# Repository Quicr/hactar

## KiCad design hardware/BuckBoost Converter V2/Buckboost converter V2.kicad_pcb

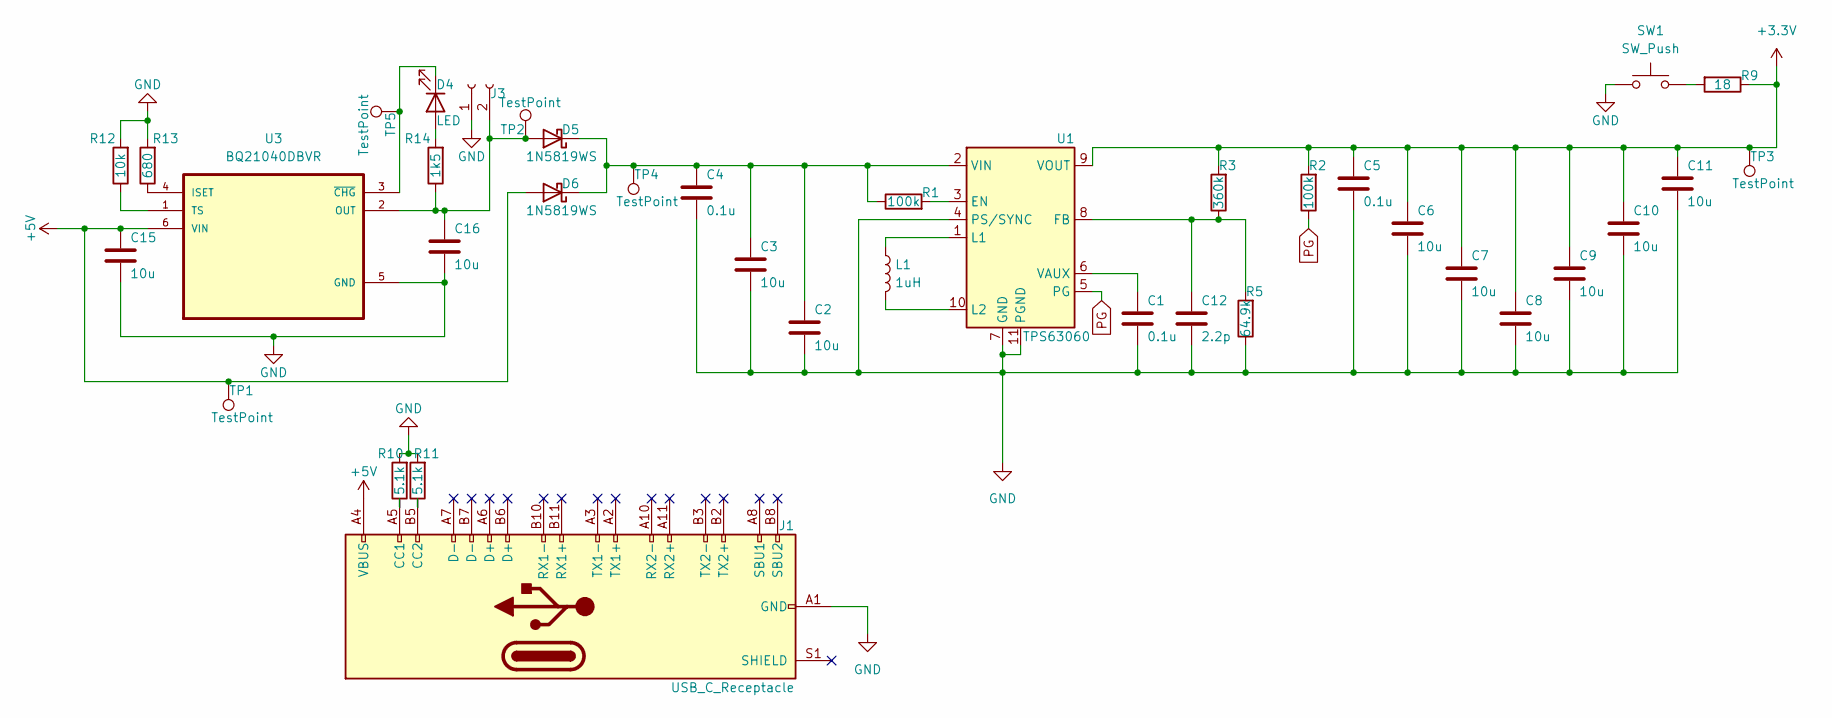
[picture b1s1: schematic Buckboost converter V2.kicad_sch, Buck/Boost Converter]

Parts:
C1, C4, C5: 0.1u; C_0805_2012Metric
C2, C3, C6, C7, C8, C9, C10, C11, C15, C16: 10u; C_0805_2012Metric
C12: 2.2p; C_0805_2012Metric
D4: LED; D_0805_2012Metric
D5, D6: 1N5819WS; D_SOD-323
J1: USB_C_Receptacle; USB_C_Receptacle_HRO_TYPE-C-31-M-12
J3: Conn_01x02_Socket; JST_PH_S2B-PH-SM4-TB_1x02-1MP_P2.00mm_Horizontal
L1: 1uH; L_0805_2012Metric
R1, R2: 100k; R_0402_1005Metric
R3: 360k; R_0402_1005Metric
R5: 64.9k; R_0402_1005Metric
R9: 18; R_1218_3246Metric
R10, R11: 5.1k; R_0402_1005Metric
R12: 10k; R_0805_2012Metric
R13: 680; R_0805_2012Metric
R14: 1k5; R_0805_2012Metric
SW1: SW_Push; SW_DIP_SPSTx01_Slide_6.7x4.1mm_W6.73mm_P2.54mm_LowProfile_J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
TP1, TP2, TP3, TP4, TP5: TestPoint; TestPoint_THTPad_D2.0mm_Drill1.0mm
U1: TPS63060; Texas_S-PWSON-N10_ThermalVias
U3: BQ21040DBVR; SOT95P280X145-6N

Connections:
+3.3V: C5.1, C6.1, C7.1, C8.1, C9.1, C10.1, C11.1, R2.2, R3.2, R9.1, TP3.1, U1.9 (VOUT)
+5V: C15.1, D6.2 (A), J1.A4 (VBUS), J1.A9 (VBUS), J1.B4 (VBUS), J1.B9 (VBUS), TP1.1, U3.6 (VIN)
GND: C1.2, C2.2, C3.2, C4.2, C5.2, C6.2, C7.2, C8.2, C9.2, C10.2, C11.2, C12.2, C15.2, C16.2, J1.A1 (GND), J1.A12 (GND), J1.B1 (GND), J1.B12 (GND), J3.1, R5.1, R10.2, R11.2, R12.2, R13.2, SW1.1, U1.4 (PS/SYNC), U1.7 (GND), U1.11 (PGND), U3.5 (GND)
unnamed: D4.2 (A), R14.2
unnamed: D4.1 (K), TP5.1, U3.3 (~CHG)
unnamed: C16.1, D5.2 (A), J3.2, R14.1, TP2.1, U3.2 (OUT)
unnamed: C2.1, C3.1, C4.1, D5.1 (K), D6.1 (K), R1.1, TP4.1, U1.2 (VIN)
unnamed: J1.A5 (CC1), R10.1
unnamed: J1.B5 (CC2), R11.1
unnamed: R9.2, SW1.2
unnamed: R1.2, U1.3 (EN)
unnamed: C12.1, R3.1, R5.2, U1.8 (FB)
unnamed: L1.1, U1.1 (L1)
unnamed: L1.2, U1.10 (L2)
unnamed: C1.1, U1.6 (VAUX)
unnamed: R13.1, U3.4 (ISET)
unnamed: R12.1, U3.1 (TS)
PG: R2.1, U1.5 (PG)

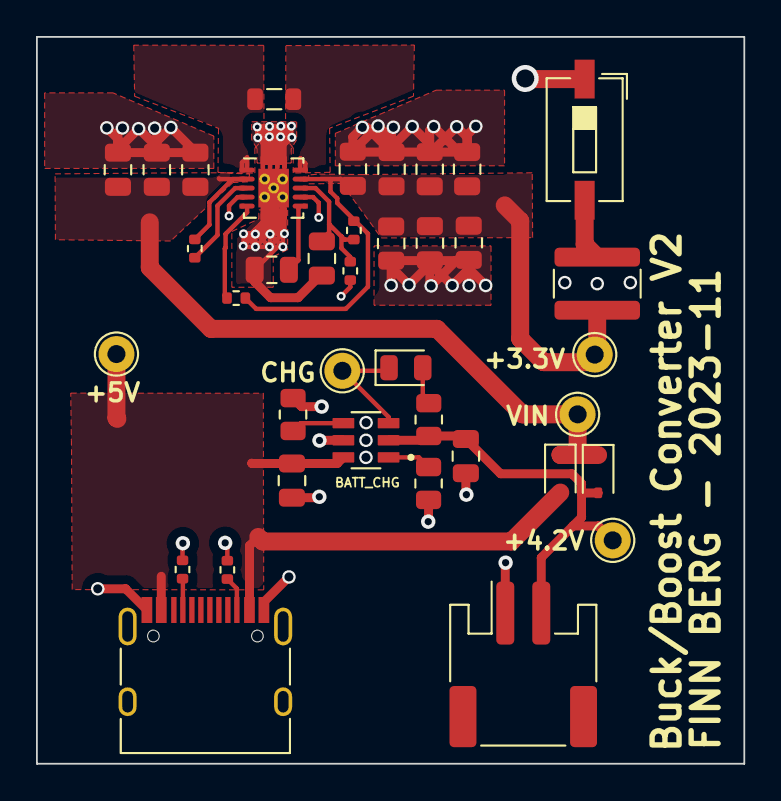
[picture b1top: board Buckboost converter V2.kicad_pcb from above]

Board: 2 copper layers, 39.3 x 40.4 mm, 38 parts (0 on the bottom side), 18 nets.

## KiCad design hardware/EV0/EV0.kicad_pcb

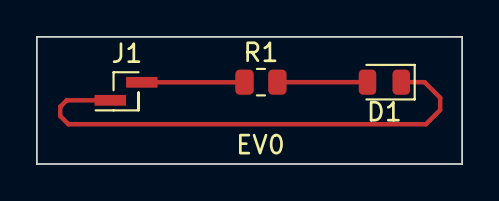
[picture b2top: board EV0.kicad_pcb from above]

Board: 2 copper layers, 23.6 x 7.1 mm, 3 parts (0 on the bottom side), 3 nets.

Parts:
D1: LED; LED_0805_2012Metric
J1: 5V; PinHeader_1x02_P1.00mm_Vertical_SMD_Pin1Right
R1: 470; R_0805_2012Metric

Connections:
unnamed: D1.1 (K), J1.1
unnamed: D1.2 (A), R1.2
unnamed: J1.2, R1.1

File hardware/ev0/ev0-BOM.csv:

"""Designator"";""Package"";""Quantity"";""Designation"";""Supplier and ref"";"
"1;""5V"";""PinHeader_1x02_P2.54mm_Vertical"";1;""5V"";;;"
"2;""D1"";""LED_0805_2012Metric"";1;""LED"";;;"
"3;""R1"";""R_0805_2012Metric"";1;""145"";;;"

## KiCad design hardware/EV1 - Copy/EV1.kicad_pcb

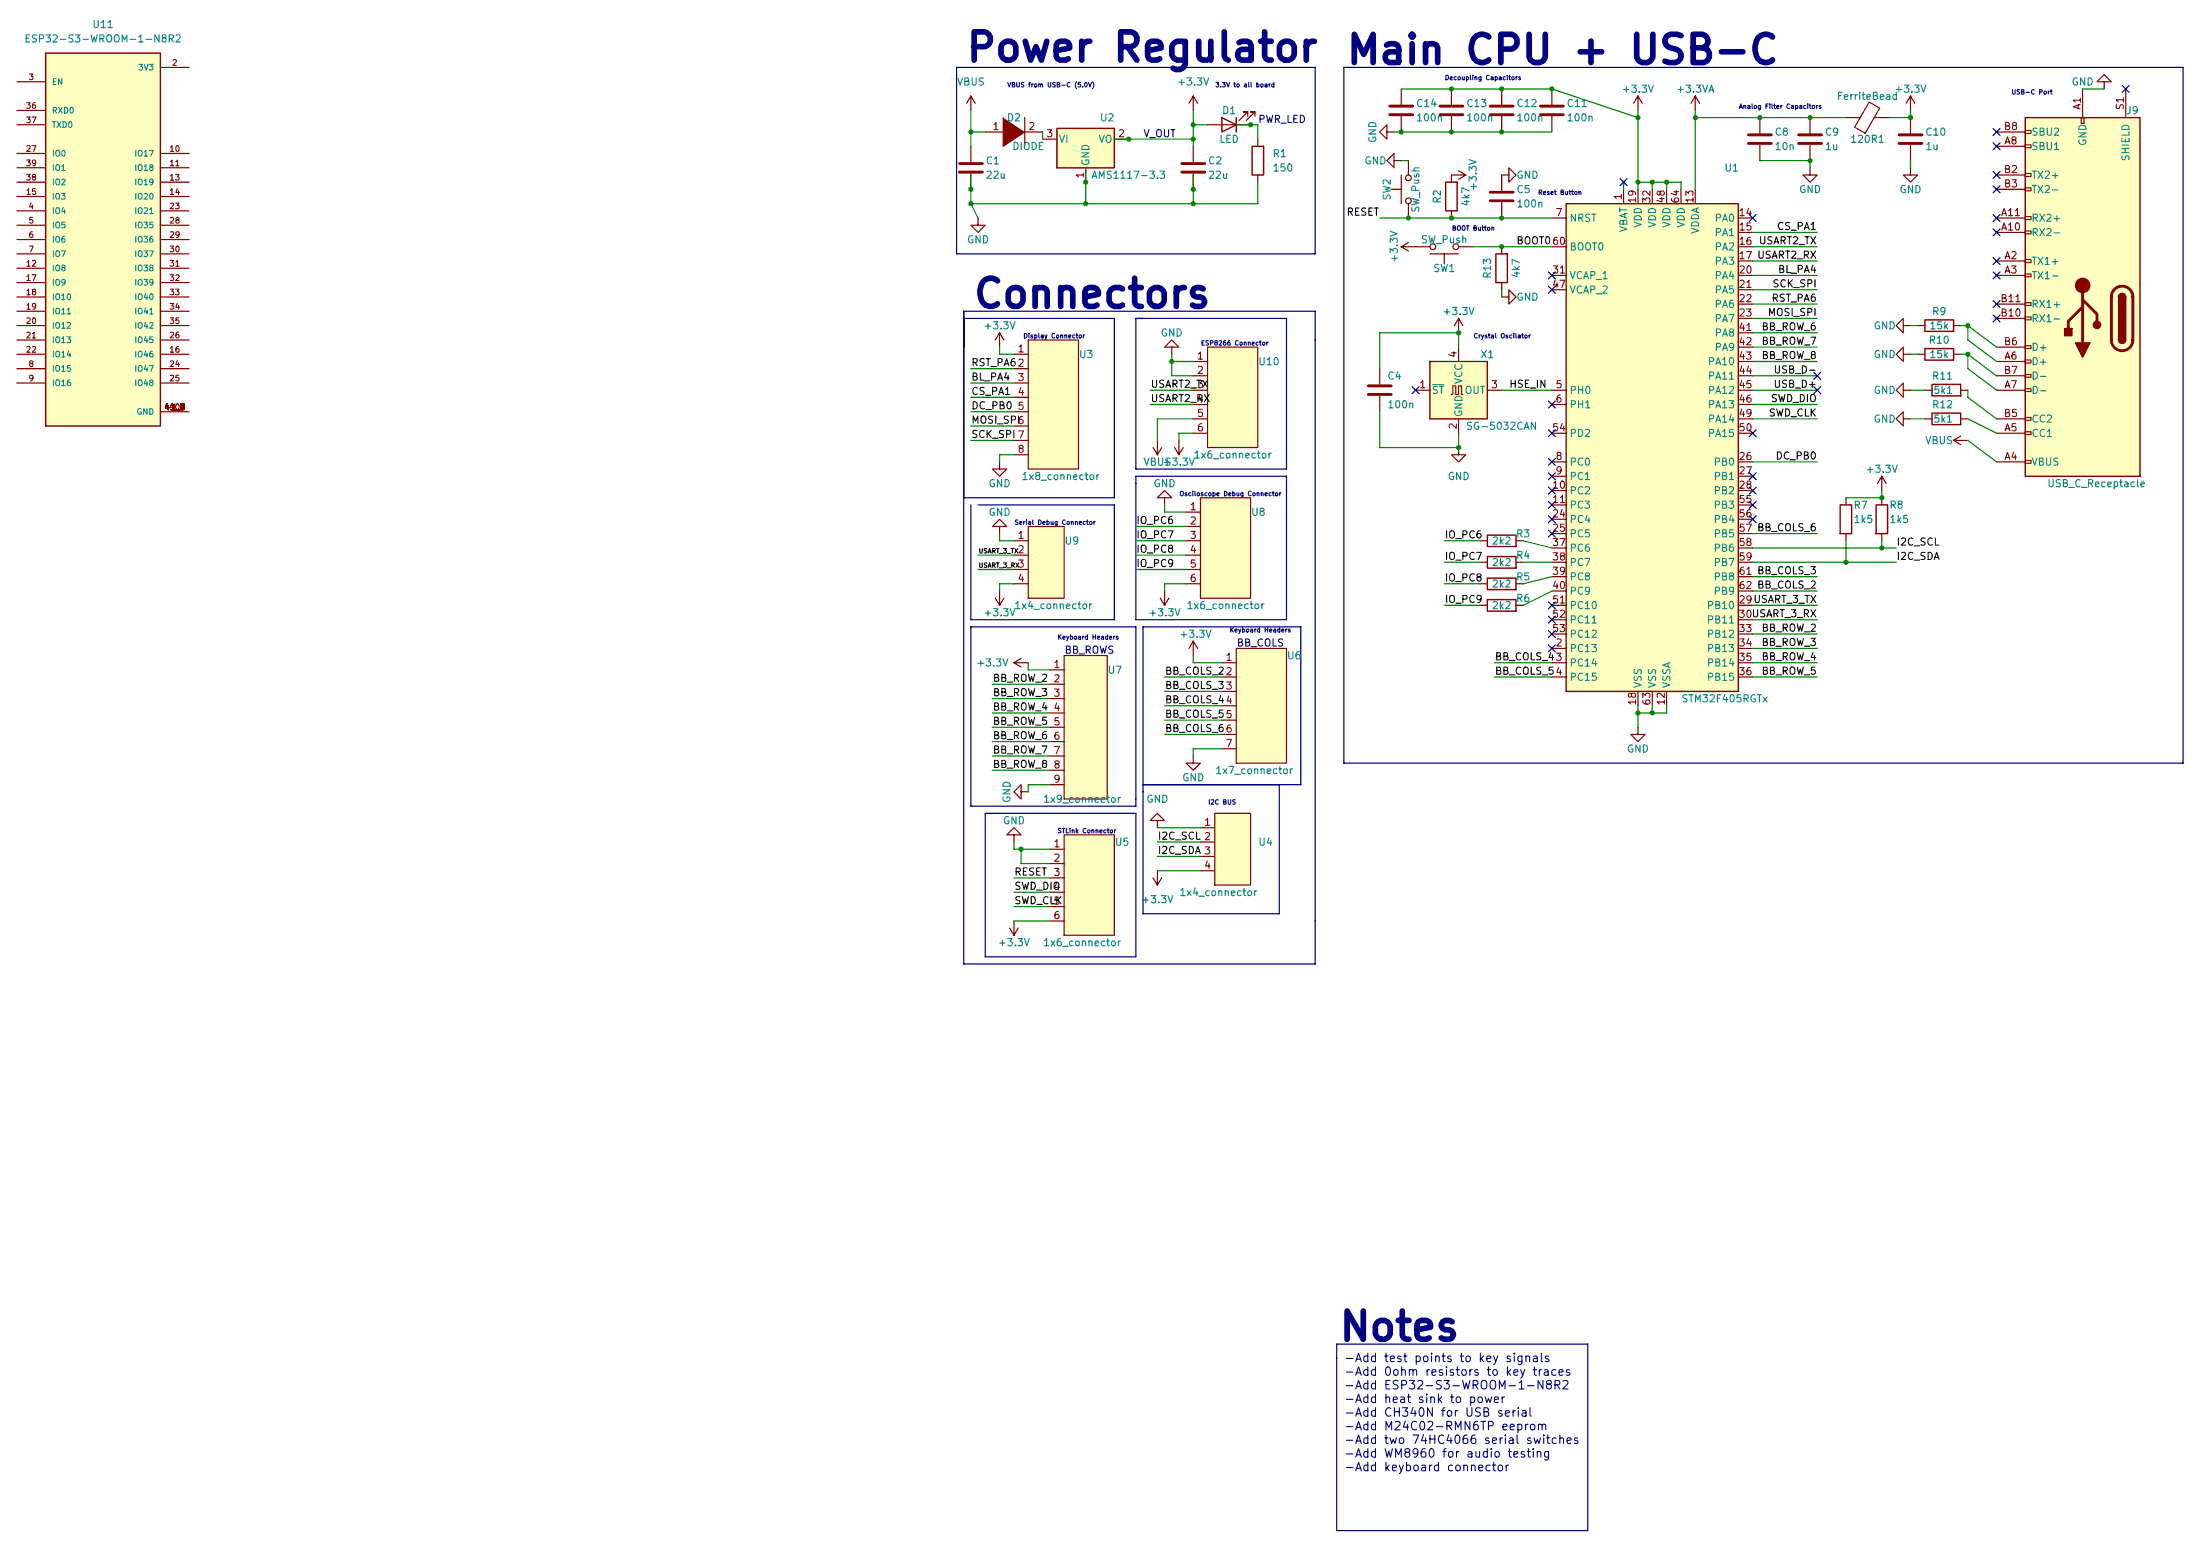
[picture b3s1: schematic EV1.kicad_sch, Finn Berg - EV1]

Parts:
120R1: FerriteBead; L_0805_2012Metric
C1, C2: 22u; C_0805_2012Metric
C4, C5, C11, C12, C13, C14: 100n; C_0805_2012Metric
C8: 10n; C_0805_2012Metric
C9, C10: 1u; C_0805_2012Metric
D1: LED; LED_0805_2012Metric
D2: DIODE; D_0805_2012Metric
J9: USB_C_Receptacle; USB_C_Receptacle_HRO_TYPE-C-31-M-12
R1: 150; R_0805_2012Metric
R2, R13: 4k7; R_0805_2012Metric
R3, R4, R5, R6: 2k2; R_0805_2012Metric
R7, R8: 1k5; R_0805_2012Metric
R9, R10: 15k; R_0805_2012Metric
R11, R12: 5k1; R_0805_2012Metric
SW1, SW2: SW_Push; SW_DIP_SPSTx01_Slide_6.7x4.1mm_W6.73mm_P2.54mm_LowProfile_J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
U1: STM32F405RGTx; LQFP-64_10x10mm_P0.5mm
U2: AMS1117-3.3; SOT-223-3_TabPin2
U3: 1x8_connector; 1X8_CONNECTOR
U4, U9: 1x4_connector
U5, U8, U10: 1x6_connector
U6: 1x7_connector
U7: 1x9_connector
U11: ESP32-S3-WROOM-1-N8R2
X1: SG-5032CAN; Oscillator_SMD_SeikoEpson_SG8002LB-4Pin_5.0x3.2mm

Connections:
+3.3V: 120R1.2, C2.1, C4.1, C10.1, C11.1, C12.1, C13.1, C14.1, D1.2 (A), R2.2, R7.1, R8.1, SW1.1, U1.19 (VDD), U1.32 (VDD), U1.48 (VDD), U1.64 (VDD), U2.2 (VO), U3.1, U4.4, U5.6, U6.1, U7.1, U8.6, U9.4, U10.6, X1.4 (VCC)
+3.3VA: 120R1.1, C8.1, C9.1, U1.13 (VDDA)
/BB_COLS_2: U1.62 (PB9), U6.2
/BB_COLS_3: U1.61 (PB8), U6.3
/BB_COLS_4: U1.3 (PC14), U6.4
/BB_COLS_5: U1.4 (PC15), U6.5
/BB_COLS_6: U1.57 (PB5), U6.6
/BB_ROW_2: U1.33 (PB12), U7.2
/BB_ROW_3: U1.34 (PB13), U7.3
/BB_ROW_4: U1.35 (PB14), U7.4
/BB_ROW_5: U1.36 (PB15), U7.5
/BB_ROW_6: U1.41 (PA8), U7.6
/BB_ROW_7: U1.42 (PA9), U7.7
/BB_ROW_8: U1.43 (PA10), U7.8
/BL_PA4: U1.20 (PA4), U3.3
/BOOT0: R13.2, SW1.2, U1.60 (BOOT0)
/CS_PA1: U1.15 (PA1), U3.4
/DC_PB0: U1.26 (PB0), U3.5
/HSE_IN: U1.5 (PH0), X1.3 (OUT)
/I2C_SCL: R8.2, U1.58 (PB6), U4.2
/I2C_SDA: R7.2, U1.59 (PB7), U4.3
/IO_PC6: R3.1, U8.2
/IO_PC7: R4.1, U8.3
/IO_PC8: R5.1, U8.4
/IO_PC9: R6.1, U8.5
/MOSI_SPI: U1.23 (PA7), U3.6
/RESET: C5.2, R2.1, SW2.2, U1.7 (NRST), U5.3
/RST_PA6: U1.22 (PA6), U3.2
/SCK_SPI: U1.21 (PA5), U3.7
/SWD_CLK: U1.49 (PA14), U5.5
/SWD_DIO: U1.46 (PA13), U5.4
/USART2_RX: U1.17 (PA3), U10.4
/USART2_TX: U1.16 (PA2), U10.3
/USART_3_RX: U1.30 (PB11), U9.3
/USART_3_TX: U1.29 (PB10), U9.2
/USB_D+: U1.45 (PA12)
/USB_D-: U1.44 (PA11)
GND: C1.2, C2.2, C4.2, C5.1, C8.2, C9.2, C10.2, C11.2, C12.2, C13.2, C14.2, J9.A1 (GND), J9.A12 (GND), J9.B1 (GND), J9.B12 (GND), R1.1, R9.1, R10.1, R11.1, R12.1, R13.1, SW2.1, U1.12 (VSSA), U1.18 (VSS), U1.63 (VSS), U2.1 (GND), U3.8, U4.1, U5.1, U5.2, U6.7, U7.9, U8.1, U9.1, U10.1, U10.2, X1.2 (GND)
unnamed: D1.1 (K), R1.2
unnamed: D2.2 (A), U2.3 (VI)
unnamed: J9.A5 (CC1), R12.2
unnamed: J9.A6 (D+), J9.B6 (D+), R9.2
unnamed: J9.A7 (D-), J9.B7 (D-), R10.2
unnamed: J9.B5 (CC2), R11.2
unnamed: R3.2, U1.37 (PC6)
unnamed: R4.2, U1.38 (PC7)
unnamed: R5.2, U1.39 (PC8)
unnamed: R6.2, U1.40 (PC9)
unnamed: U11.1 (GND), U11.40 (GND), U11.41_1 (GND), U11.41_2 (GND), U11.41_3 (GND), U11.41_4 (GND), U11.41_5 (GND), U11.41_6 (GND), U11.41_7 (GND), U11.41_8 (GND), U11.41_9 (GND)
VBUS: C1.1, D2.1 (K), J9.A4 (VBUS), J9.A9 (VBUS), J9.B4 (VBUS), J9.B9 (VBUS), U10.5

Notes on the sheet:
Notes
Osciloscope Debug Connector
BOOT Button
STLink Connector
-Add test points to key signals -Add 0ohm resistors to key traces -Add ESP32-S3-WROOM-1-N8R2 -Add heat sink to power -Add CH340N for USB serial -Add M24C02-RMN6TP eeprom -Add two 74HC4066 serial switches -Add WM8960 for audio testing -Add keyboard connector
Power Regulator
V_OUT
BB_ROWS
Display Connector
Main CPU + USB-C
BB_COLS
PWR_LED
Keyboard Headers
Decoupling Capacitors
Reset Button
Serial Debug Connector
VBUS from USB-C (5.0V)
Connectors
3.3V to all board
Analog Filter Capacitors
I2C BUS
Crystal Oscilator
ESP8266 Connector
USB-C Port

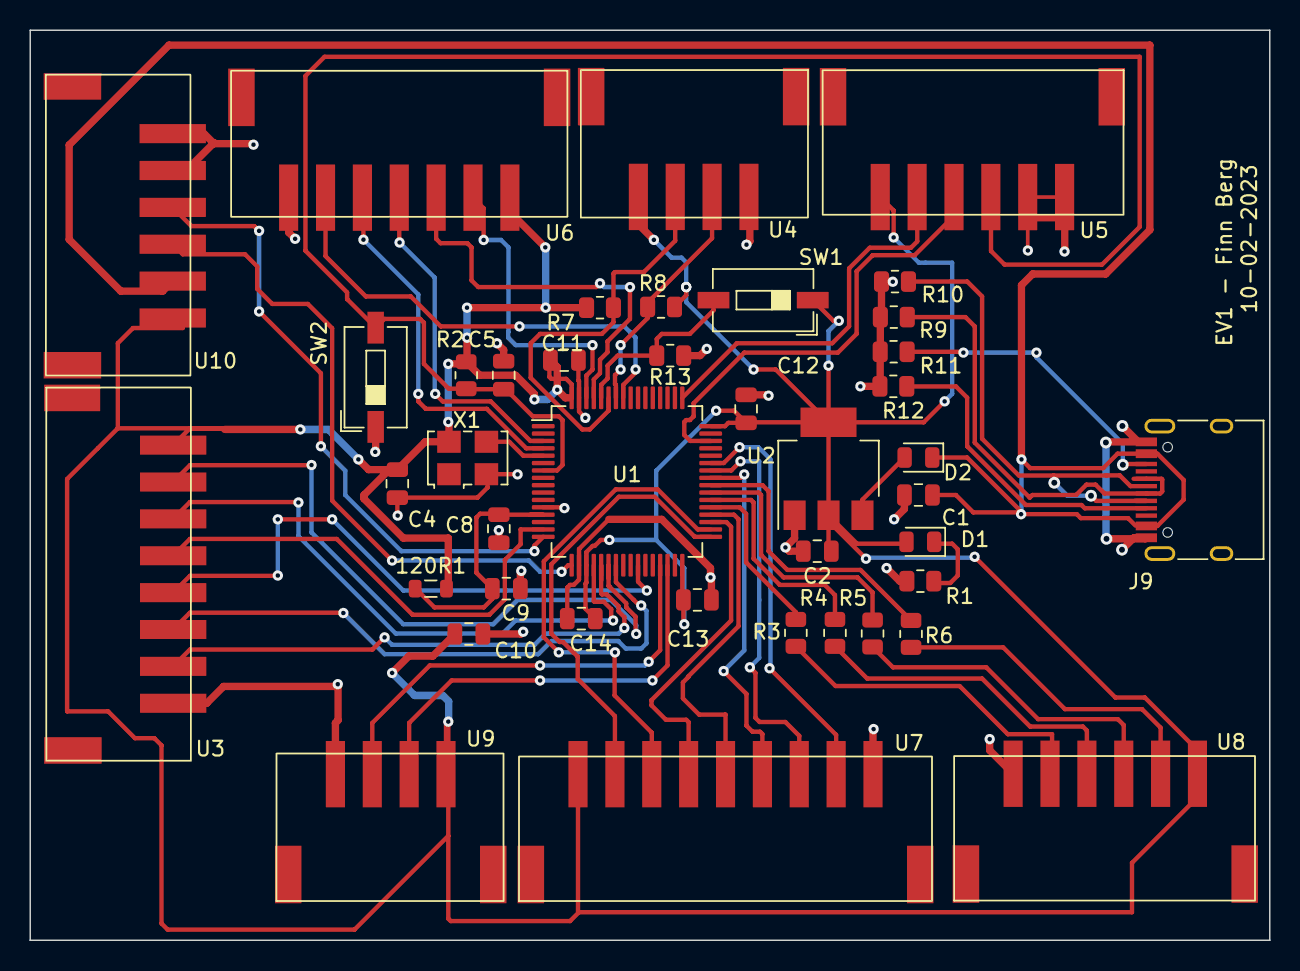
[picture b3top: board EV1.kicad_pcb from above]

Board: 2 copper layers, 84.0 x 61.7 mm, 41 parts (0 on the bottom side), 47 nets.

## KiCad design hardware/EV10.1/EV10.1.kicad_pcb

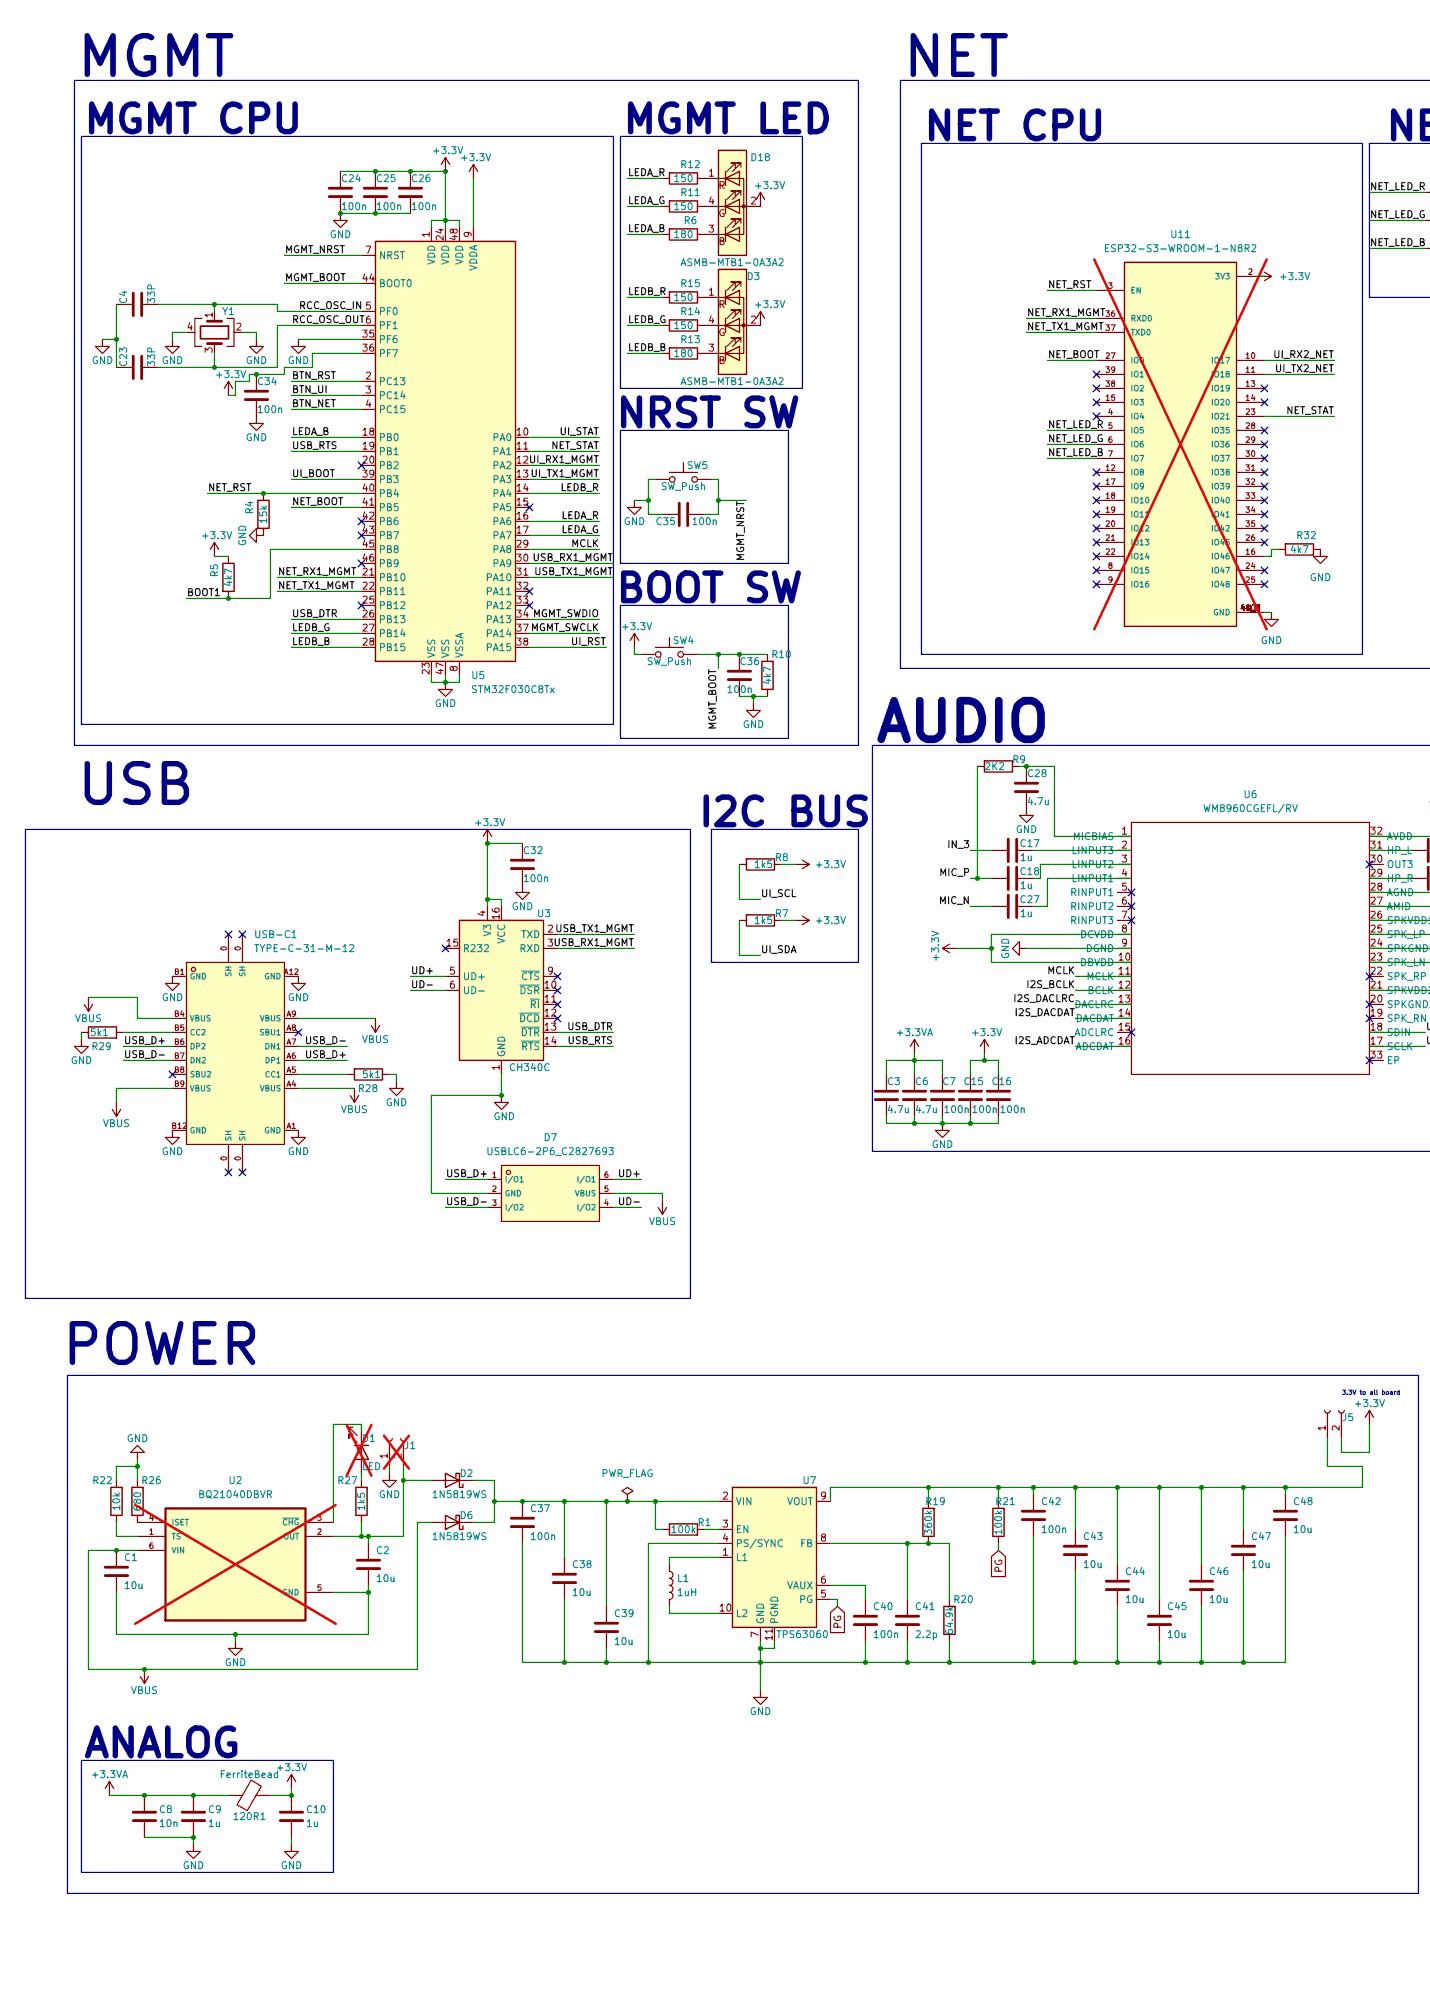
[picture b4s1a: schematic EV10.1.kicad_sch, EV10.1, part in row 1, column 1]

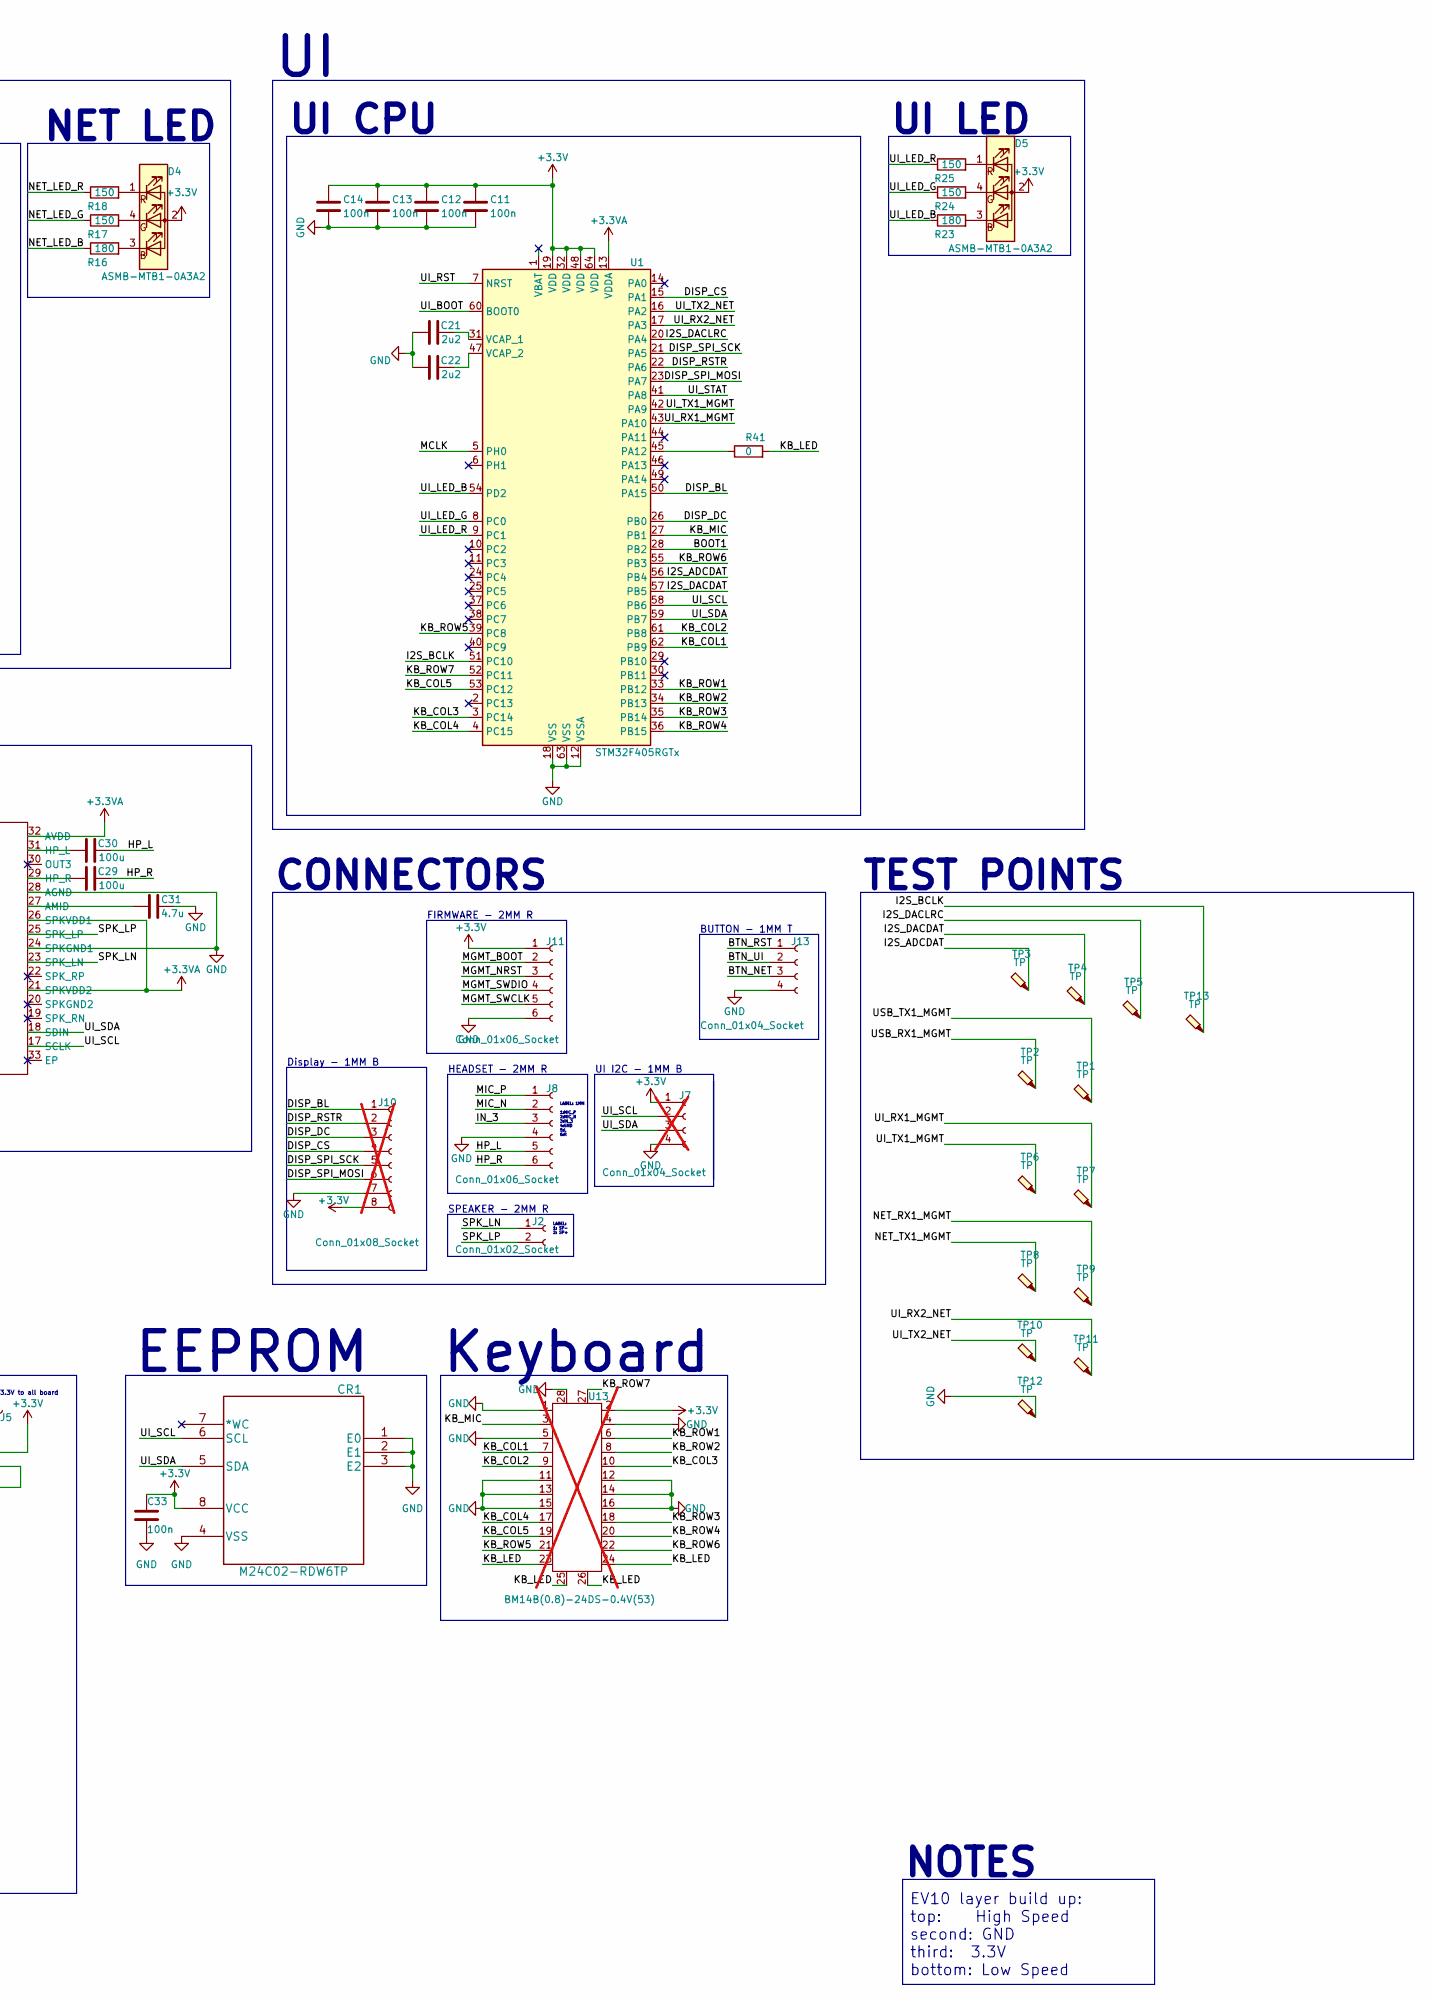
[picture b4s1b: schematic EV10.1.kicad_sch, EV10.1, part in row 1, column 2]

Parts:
120R1: FerriteBead; L_0603_1608Metric; JLCPCB# C127301
C1, C2: 10u; C_0402_1005Metric; JLCPCB# C15525
C3, C6, C28, C31: 4.7u; C_0402_1005Metric; JLCPCB# C23733
C4, C23: 33P; C_0805_2012Metric; JLCPCB# C107115
C7, C11, C12, C13, C14, C15, C16, C24, C25, C26, C32, C33, C34, C35, C36: 100n; C_0402_1005Metric; JLCPCB# C1525
C8: 10n; C_0402_1005Metric; JLCPCB# C15195
C9, C10, C17, C18, C27: 1u; C_0402_1005Metric; JLCPCB# C52923
C21, C22: 2u2; C_0402_1005Metric; JLCPCB# C12530
C29, C30: 100u; C_1206_3216Metric; JLCPCB# C15008
C37, C40, C42: 100n; C_0805_2012Metric; JLCPCB# C49678
C38, C39, C43, C44, C45, C46, C47, C48: 10u; C_0805_2012Metric; JLCPCB# C15850
C41: 2.2p; C_0805_2012Metric; JLCPCB# C519933
CR1: M24C02-RDW6TP; New_ESP32_M24C02-RMN6TP; JLCPCB Rotation Offset -90
D1: LED; D_0805_2012Metric; JLCPCB# C185403; not fitted
D2, D6: 1N5819WS; D_SOD-323; JLCPCB# C191023
D3, D4, D5, D18: ASMB-MTB1-0A3A2; LED RGB; JLCPCB Position Offset 0.70,0.35
D7: USBLC6-2P6_C2827693; SOT-666-6_L1.6-W1.2-P0.50-LS1.6-BL; JLCPCB# C2827693
J1: Conn_01x02_Socket; JST_PH_S2B-PH-SM4-TB_1x02-1MP_P2.00mm_Horizontal; JLCPCB Rotation Offset 180; not fitted
J2, J5: Conn_01x02_Socket; JST_PH_S2B-PH-SM4-TB_1x02-1MP_P2.00mm_Horizontal; JLCPCB Rotation Offset 180
J7: Conn_01x04_Socket; 1x4pin 1mm connector; JLCPCB Position Offset 2.59,1.73; not fitted
J8, J11: Conn_01x06_Socket; JST_PH_S6B-PH-SM4-TB_1x06-1MP_P2.00mm_Horizontal; JLCPCB# C265405
J10: Conn_01x08_Socket; JST_SHL_SM08B-SHLS-TF_1x08-1MP_P1.00mm_Horizontal; JLCPCB# C3029349; not fitted
J13: Conn_01x04_Socket; 1x4pin 1mm connector; JLCPCB Position Offset 2.59,1.73
L1: 1uH; L_0805_2012Metric; JLCPCB# C370013
R1, R21: 100k; R_0402_1005Metric; JLCPCB# C25741
R4: 15k; R_0402_1005Metric; JLCPCB# C25756
R5, R10, R32: 4k7; R_0402_1005Metric; JLCPCB# C25900
R6, R13, R16, R23: 180; R_0402_1005Metric; JLCPCB# C25087
R7, R8, R27: 1k5; R_0402_1005Metric; JLCPCB# C25867
R9: 2K2; R_0402_1005Metric; JLCPCB# C25879
R11, R12, R14, R15, R17, R18, R24, R25: 150; R_0402_1005Metric; JLCPCB# C25082
R19: 360k; R_0402_1005Metric; JLCPCB# C170299
R20: 64.9k; R_0402_1005Metric; JLCPCB# C185403
R22: 10k; R_0402_1005Metric; JLCPCB# C25744
R26: 680; R_0402_1005Metric; JLCPCB# C25130
R28, R29: 5k1; R_0402_1005Metric; JLCPCB# C25905
R41: 0; R_0402_1005Metric; JLCPCB# C17168
SW4, SW5: SW_Push; SW_DIP_SPSTx01_Slide_6.7x4.1mm_W6.73mm_P2.54mm_LowProfile_J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; JLCPCB# C266189
TP1, TP2, TP3, TP4, TP5, TP6, TP7, TP8, TP9, TP10, TP11, TP12, TP13: TP; TestPoint_Keystone_5000-5004_Miniature; JLCPCB# C5199900
U1: STM32F405RGTx; LQFP-64_10x10mm_P0.5mm; JLCPCB# C15742
U2: BQ21040DBVR; SOT-23-6; JLCPCB Rotation Offset 180; not fitted
U3: CH340C; SOIC-16_3.9x9.9mm_P1.27mm; JLCPCB# C84681
U5: STM32F030C8Tx; LQFP-48_7x7mm_P0.5mm; JLCPCB# C80488
U6: WM8960CGEFL/RV; QFN50P500X500X90-33N; JLCPCB# C18752
U7: TPS63060; Texas_S-PWSON-N10_ThermalVias; JLCPCB Rotation Offset -90
U11: ESP32-S3-WROOM-1-N8R2; ESP32-S3-WROOM-1U; JLCPCB# C3013944; not fitted
U13: BM14B(0.8)-24DS-0.4V(53); BM14B(0.B)-24DS-0.4V(53); JLCPCB# C3640874; not fitted
USB-C1: TYPE-C-31-M-12; USB-C_SMD-TYPE-C-31-M-12; JLCPCB Position Offset 0, 1.0
Y1: Crystal_GND24; Crystal_SMD_3225-4Pin_3.2x2.5mm; JLCPCB# C13738

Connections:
+3.3V: 120R1.2, C10.1, C11.1, C12.1, C13.1, C14.1, C15.2, C16.2, C24.1, C25.1, C26.1, C32.1, C33.1, C34.1, CR1.8 (VCC), D3.2 (A), D4.2 (A), D5.2 (A), D18.2 (A), J5.2, J7.1, J10.8, J11.1, R5.1, R7.1, R8.1, SW4.2, U1.19 (VDD), U1.32 (VDD), U1.48 (VDD), U1.64 (VDD), U3.4 (V3), U3.16 (VCC), U5.1 (VDD), U5.9 (VDDA), U5.24 (VDD), U5.36 (PF7), U5.48 (VDD), U6.8 (DCVDD), U6.10 (DBVDD), U11.2 (3V3), U13.2
+3.3VA: 120R1.1, C3.1, C6.1, C7.2, C8.1, C9.1, U1.13 (VDDA), U6.21 (SPKVDD2), U6.26 (SPKVDD1), U6.32 (AVDD)
/BOOT1: R5.2, U1.28 (PB2), U5.45 (PB8)
/BTN_NET: J13.3, U5.4 (PC15)
/BTN_RST: J13.1, U5.2 (PC13)
/BTN_UI: J13.2, U5.3 (PC14)
/DISP_BL: J10.1, U1.50 (PA15)
/DISP_CS: J10.4, U1.15 (PA1)
/DISP_DC: J10.3, U1.26 (PB0)
/DISP_RSTR: J10.2, U1.22 (PA6)
/DISP_SPI_MOSI: J10.6, U1.23 (PA7)
/DISP_SPI_SCK: J10.5, U1.21 (PA5)
/HP_L: C30.2, J8.5
/HP_R: C29.2, J8.6
/I2S_ADCDAT: TP3.1, U1.56 (PB4), U6.16 (ADCDAT)
/I2S_BCLK: TP13.1, U1.51 (PC10), U6.12 (BCLK)
/I2S_DACDAT: TP4.1, U1.57 (PB5), U6.14 (DACDAT)
/I2S_DACLRC: TP5.1, U1.20 (PA4), U6.13 (DACLRC)
/IN_3: C17.1, J8.3
/KB_COL1: U1.62 (PB9), U13.7
/KB_COL2: U1.61 (PB8), U13.9
/KB_COL3: U1.3 (PC14), U13.10
/KB_COL4: U1.4 (PC15), U13.17
/KB_COL5: U1.53 (PC12), U13.19
/KB_LED: R41.2, U13.23, U13.24, U13.25, U13.26
/KB_MIC: U1.27 (PB1), U13.3
/KB_ROW1: U1.33 (PB12), U13.6
/KB_ROW2: U1.34 (PB13), U13.8
/KB_ROW3: U1.35 (PB14), U13.18
/KB_ROW4: U1.36 (PB15), U13.20
/KB_ROW5: U1.39 (PC8), U13.21
/KB_ROW6: U1.55 (PB3), U13.22
/KB_ROW7: U1.52 (PC11), U13.27
/LEDA_B: R6.2, U5.18 (PB0)
/LEDA_G: R11.2, U5.17 (PA7)
/LEDA_R: R12.2, U5.16 (PA6)
/LEDB_B: R13.2, U5.28 (PB15)
/LEDB_G: R14.2, U5.27 (PB14)
/LEDB_R: R15.2, U5.14 (PA4)
/MCLK: U1.5 (PH0), U5.29 (PA8), U6.11 (MCLK)
/MGMT_BOOT: C36.2, J11.2, R10.2, SW4.1, U5.44 (BOOT0)
/MGMT_NRST: C35.2, J11.3, SW5.1, U5.7 (NRST)
/MGMT_SWCLK: J11.5, U5.37 (PA14)
/MGMT_SWDIO: J11.4, U5.34 (PA13)
/MIC_N: C27.1, J8.2
/MIC_P: C18.1, J8.1, R9.2
/NET_BOOT: U5.41 (PB5), U11.27 (IO0)
/NET_LED_B: R16.1, U11.7 (IO7)
/NET_LED_G: R17.1, U11.6 (IO6)
/NET_LED_R: R18.1, U11.5 (IO5)
/NET_RST: R4.1, U5.40 (PB4), U11.3 (EN)
/NET_RX1_MGMT: TP9.1, U5.21 (PB10), U11.36 (RXD0)
/NET_STAT: U5.11 (PA1), U11.23 (IO21)
/NET_TX1_MGMT: TP8.1, U5.22 (PB11), U11.37 (TXD0)
/RCC_OSC_IN: C4.2, U5.5 (PF0), Y1.1
/RCC_OSC_OUT: C23.2, U5.6 (PF1), Y1.3
/SPK_LN: J2.1, U6.23 (SPK_LN)
/SPK_LP: J2.2, U6.25 (SPK_LP)
/UD+: D7.6 (I/O1), U3.5 (UD+)
/UD-: D7.4 (I/O2), U3.6 (UD-)
/UI_BOOT: U1.60 (BOOT0), U5.39 (PB3)
/UI_LED_B: R23.1, U1.54 (PD2)
/UI_LED_G: R24.1, U1.8 (PC0)
/UI_LED_R: R25.1, U1.9 (PC1)
/UI_RST: U1.7 (NRST), U5.38 (PA15)
/UI_RX1_MGMT: TP7.1, U1.43 (PA10), U5.12 (PA2)
/UI_RX2_NET: TP11.1, U1.17 (PA3), U11.10 (IO17)
/UI_SCL: CR1.6 (SCL), J7.2, R8.2, U1.58 (PB6), U6.17 (SCLK)
/UI_SDA: CR1.5 (SDA), J7.3, R7.2, U1.59 (PB7), U6.18 (SDIN)
/UI_STAT: U1.41 (PA8), U5.10 (PA0)
/UI_TX1_MGMT: TP6.1, U1.42 (PA9), U5.13 (PA3)
/UI_TX2_NET: TP10.1, U1.16 (PA2), U11.11 (IO18)
/USB_D+: D7.1 (I/O1), USB-C1.A6 (DP1), USB-C1.B6 (DP2)
/USB_D-: D7.3 (I/O2), USB-C1.A7 (DN1), USB-C1.B7 (DN2)
/USB_DTR: U3.13 (~DTR), U5.26 (PB13)
/USB_RTS: U3.14 (~RTS), U5.19 (PB1)
/USB_RX1_MGMT: TP2.1, U3.3 (RXD), U5.30 (PA9)
/USB_TX1_MGMT: TP1.1, U3.2 (TXD), U5.31 (PA10)
GND: C1.2, C2.2, C3.2, C4.1, C6.2, C7.1, C8.2, C9.2, C10.2, C11.2, C12.2, C13.2, C14.2, C15.1, C16.1, C21.1, C22.1, C23.1, C24.2, C25.2, C26.2, C28.2, C31.1, C32.2, C33.2, C34.2, C35.1, C36.1, C37.2, C38.2, C39.2, C40.2, C41.2, C42.2, C43.2, C44.2, C45.2, C46.2, C47.2, C48.2, CR1.1 (E0), CR1.2 (E1), CR1.3 (E2), CR1.4 (VSS), D7.2 (GND), J1.1, J7.4, J8.4, J10.7, J11.6, J13.4, R4.2, R10.1, R20.1, R22.2, R26.2, R28.1, R29.1, R32.1, SW5.2, TP12.1, U1.12 (VSSA), U1.18 (VSS), U1.63 (VSS), U2.5 (GND), U3.1 (GND), U5.8 (VSSA), U5.23 (VSS), U5.35 (PF6), U5.47 (VSS), U6.9 (DGND), U6.24 (SPKGND1), U6.28 (AGND), U7.4 (PS/SYNC), U7.7 (GND), U7.11 (PGND), U11.1 (GND), U11.40 (GND), U11.41_1 (GND), U11.41_2 (GND), U11.41_3 (GND), U11.41_4 (GND), U11.41_5 (GND), U11.41_6 (GND), U11.41_7 (GND), U11.41_8 (GND), U11.41_9 (GND), U13.1, U13.4, U13.5, U13.11, U13.12, U13.13, U13.14, U13.15, U13.16, U13.28, USB-C1.A1 (GND), USB-C1.A12 (GND), USB-C1.B1 (GND), USB-C1.B12 (GND), Y1.2, Y1.4
unnamed: D1.2 (A), R27.2
unnamed: D1.1 (K), U2.3 (~CHG)
unnamed: C2.1, D2.2 (A), J1.2, R27.1, U2.2 (OUT)
unnamed: C37.1, C38.1, C39.1, D2.1 (K), D6.1 (K), R1.1, U7.2 (VIN)
unnamed: D3.3 (BK), R13.1
unnamed: D3.4 (GK), R14.1
unnamed: D3.1 (RK), R15.1
unnamed: D4.3 (BK), R16.2
unnamed: D4.4 (GK), R17.2
unnamed: D4.1 (RK), R18.2
unnamed: D5.3 (BK), R23.2
unnamed: D5.4 (GK), R24.2
unnamed: D5.1 (RK), R25.2
unnamed: D18.3 (BK), R6.1
unnamed: D18.4 (GK), R11.1
unnamed: D18.1 (RK), R12.1
unnamed: C42.1, C43.1, C44.1, C45.1, C46.1, C47.1, C48.1, J5.1, R19.2, R21.2, U7.9 (VOUT)
unnamed: R41.1, U1.45 (PA12)
unnamed: C21.2, U1.31 (VCAP_1)
unnamed: C22.2, U1.47 (VCAP_2)
unnamed: R26.1, U2.4 (ISET)
unnamed: R22.1, U2.1 (TS)
unnamed: C31.2, U6.27 (AMID)
unnamed: C30.1, U6.31 (HP_L)
unnamed: C29.1, U6.29 (HP_R)
unnamed: C27.2, U6.4 (LINPUT1)
unnamed: C18.2, U6.3 (LINPUT2)
unnamed: C17.2, U6.2 (LINPUT3)
unnamed: C28.1, R9.1, U6.1 (MICBIAS)
unnamed: R1.2, U7.3 (EN)
unnamed: C41.1, R19.1, R20.2, U7.8 (FB)
unnamed: L1.1, U7.1 (L1)
unnamed: L1.2, U7.10 (L2)
unnamed: C40.1, U7.6 (VAUX)
unnamed: R32.2, U11.16 (IO46)
unnamed: R28.2, USB-C1.A5 (CC1)
unnamed: R29.2, USB-C1.B5 (CC2)
PG: R21.1, U7.5 (PG)
VBUS: C1.1, D6.2 (A), D7.5 (VBUS), U2.6 (VIN), USB-C1.A4 (VBUS), USB-C1.A9 (VBUS), USB-C1.B4 (VBUS), USB-C1.B9 (VBUS)

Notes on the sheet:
MGMT
SPEAKER - 2MM R
NET CPU
MGMT CPU
NET
POWER
CONNECTORS
NET LED
UI CPU
HEADSET - 2MM R
NRST SW
BUTTON - 1MM T
EV10 layer build up: top: High Speed second: GND third: 3.3V bottom: Low Speed
LABEL: 1MM 1:MIC_P 2:MIC_N 3:IN_3 4:GND 5:L 6:R
AUDIO
BOOT SW
EEPROM
UI I2C - 1MM B
I2C BUS
FIRMWARE - 2MM R
USB
MGMT LED
3.3V to all board
LABEL: 1: SP- 2: SP+
NOTES
Keyboard
Display - 1MM B
UI LED
TEST POINTS
ANALOG

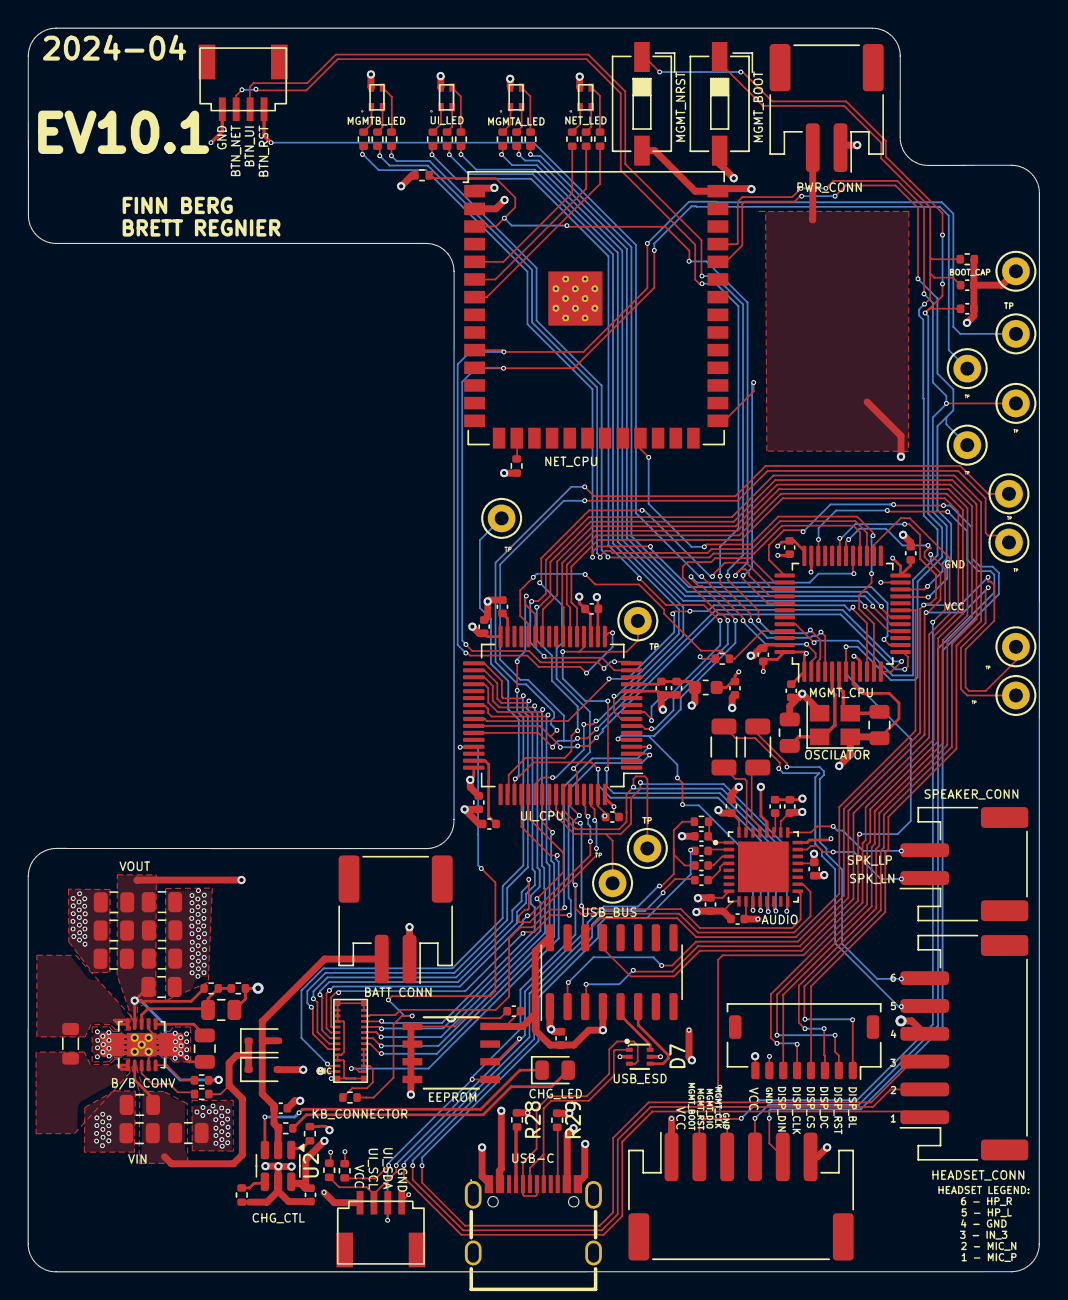
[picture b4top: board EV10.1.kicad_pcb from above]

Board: 4 copper layers, 72.7 x 89.4 mm, 118 parts (0 on the bottom side), 118 nets.
